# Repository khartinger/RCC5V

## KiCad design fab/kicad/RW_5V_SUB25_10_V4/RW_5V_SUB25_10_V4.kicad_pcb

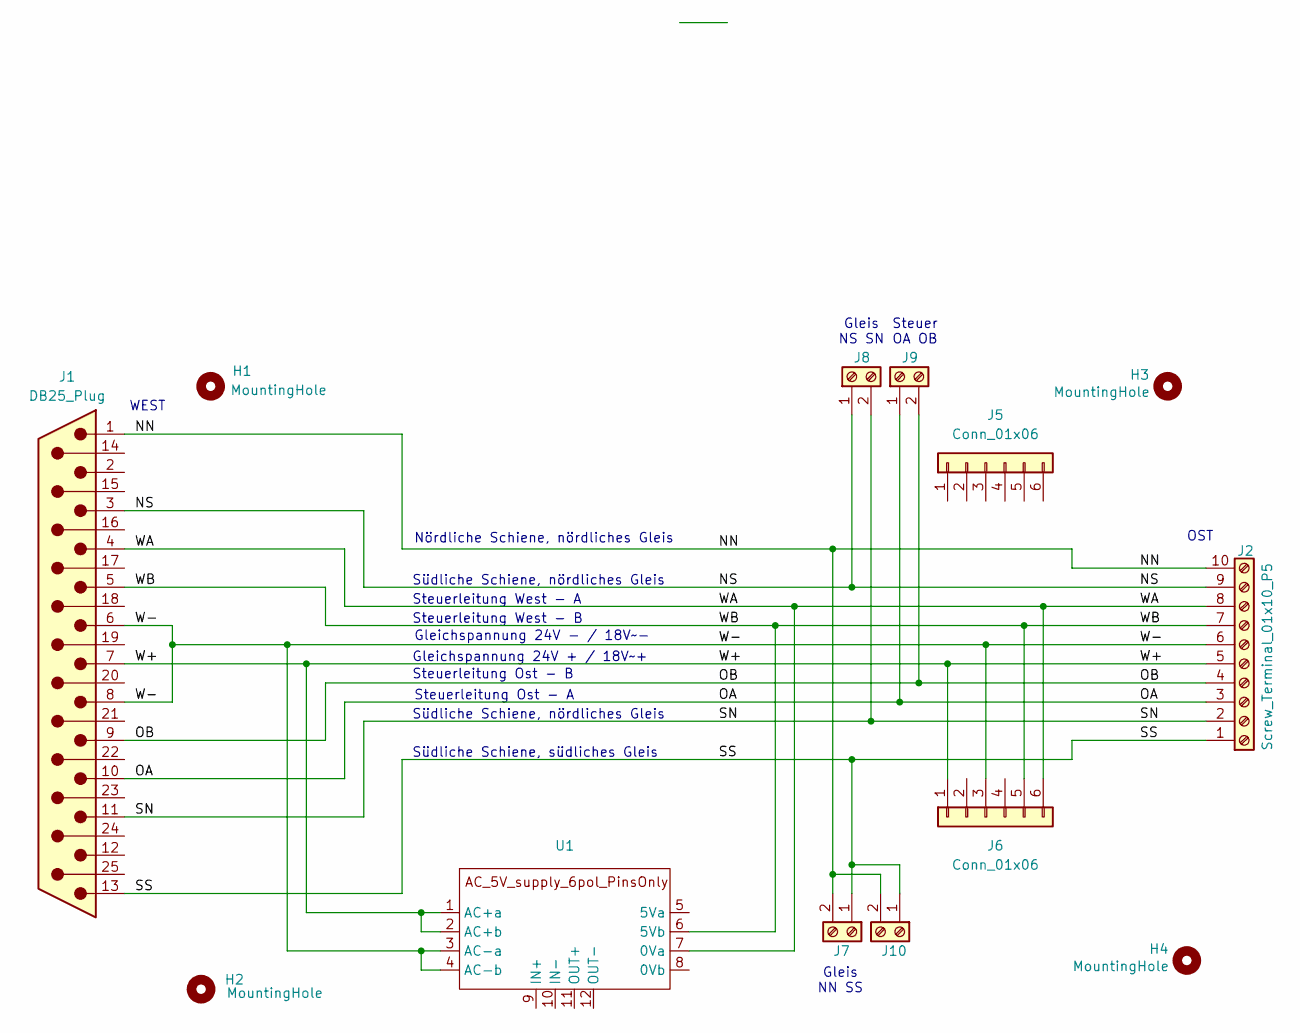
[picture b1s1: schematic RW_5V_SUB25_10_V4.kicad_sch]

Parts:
H1, H2, H3, H4: MountingHole; MountingHole_2.7mm_M2.5_DIN965_Pad_TopBottom
J1: DB25_Plug; DSUB-25_Male_Horizontal_P2.77x2.84mm_EdgePinOffset7.70mm_Ho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
J2: Screw_Terminal_01x10_P5
J5, J6: Conn_01x06; PinSocket_1x06_P2.54mm_Vertical_1.1_kh
J7, J8, J9, J10: Screw_Terminal_01x02_P5
U1: AC_5V_supply_6pol_PinsOnly

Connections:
/NN: J1.1, J2.10, J7.2, J10.2
/NS: J1.3, J2.9, J8.1
/OA: J1.10, J2.3, J9.1
/OB: J1.9, J2.4, J9.2
/SN: J1.11, J2.2, J8.2
/SS: J1.13, J2.1, J7.1, J10.1
/W+: J1.7, J2.5, J6.1, U1.1 (AC+a), U1.2 (AC+b)
/W-: J1.6, J1.8, J2.6, J6.3, U1.3 (AC-a), U1.4 (AC-b)
/WA: J1.4, J2.8, J6.6, U1.7 (0Va)
/WB: J1.5, J2.7, J6.5, U1.6 (5Vb)

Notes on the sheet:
Gleis NS SN
Südliche Schiene, südliches Gleis
Südliche Schiene, nördliches Gleis
Steuer OA OB
Gleichspannung 24V - / 18V~-
Nördliche Schiene, nördliches Gleis
Steuerleitung West - A
Steuerleitung Ost - B
Steuerleitung West - B
WEST
Gleichspannung 24V + / 18V~+
OST
Gleis NN SS
Steuerleitung Ost - A

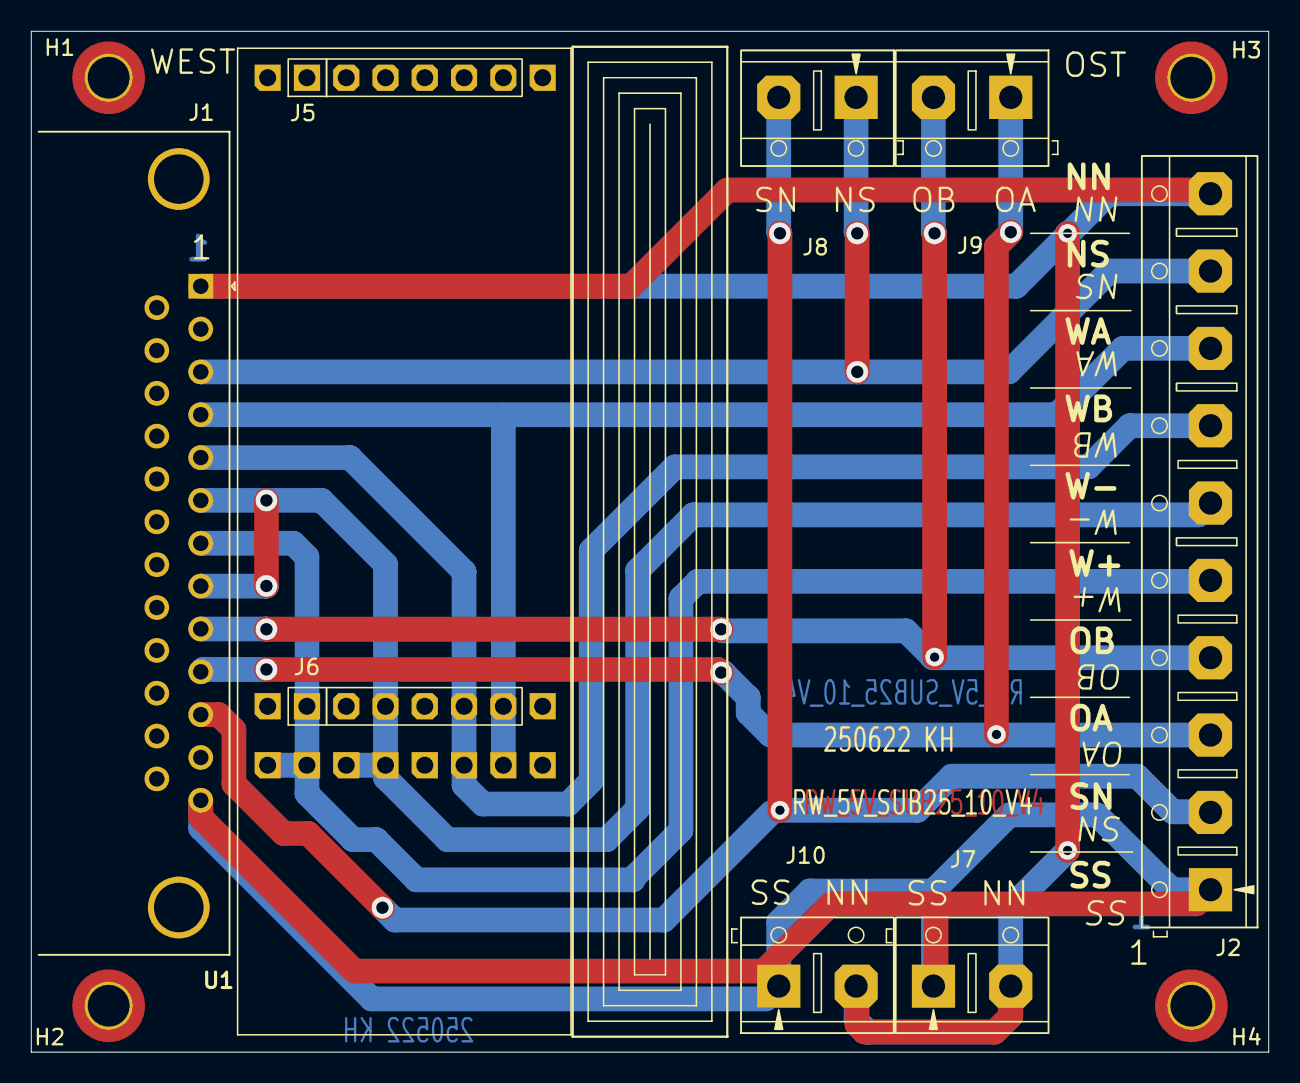
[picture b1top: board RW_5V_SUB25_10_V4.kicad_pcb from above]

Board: 2 copper layers, 80.0 x 66.0 mm, 13 parts (0 on the bottom side), 10 nets.

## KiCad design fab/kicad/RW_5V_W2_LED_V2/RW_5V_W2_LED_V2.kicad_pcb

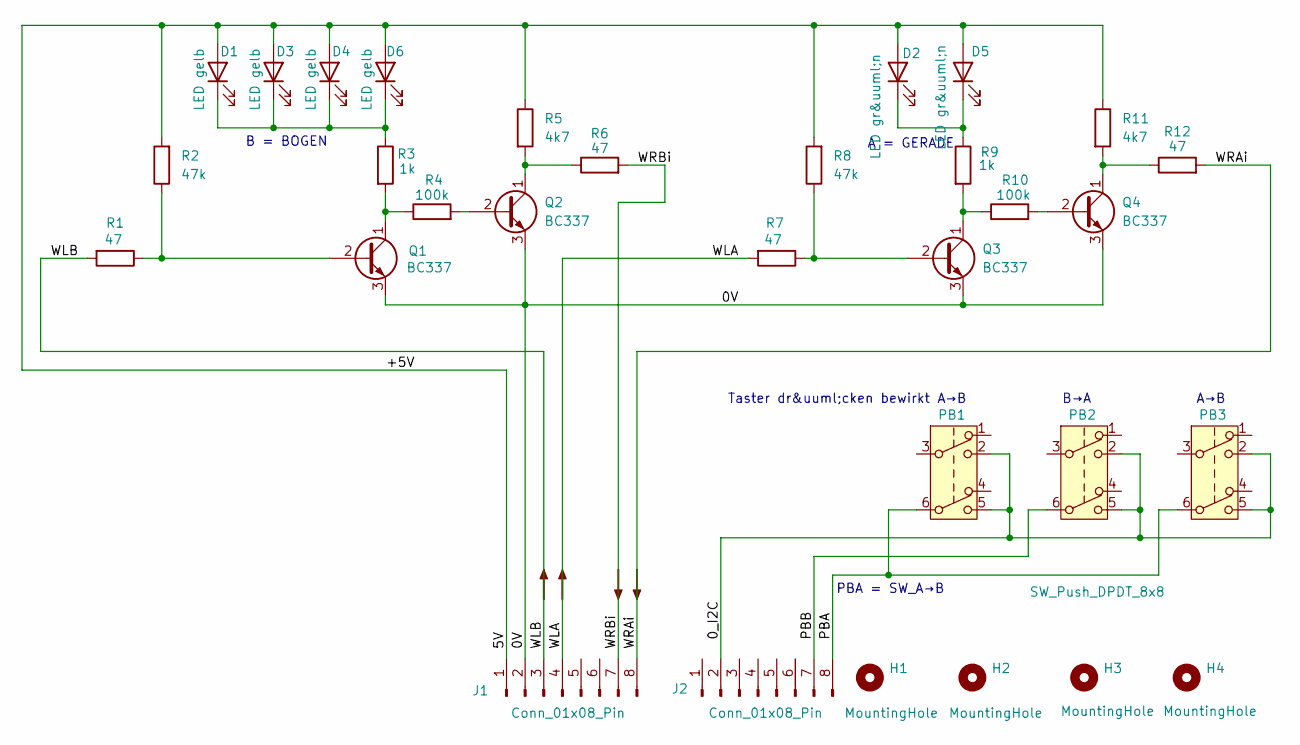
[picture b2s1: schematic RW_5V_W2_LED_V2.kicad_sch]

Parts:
D1, D3, D4, D6: LED gelb; LED_D3.0mm
D2, D5: LED gr&uuml;n; LED_D3.0mm
H1, H2, H3, H4: MountingHole; MountingHole_2.2mm_M2_Pad_TopBottom_kh
J1, J2: Conn_01x08_Pin; PinSocket_1x08_P2.54mm_Vertical_kh
PB1, PB2, PB3: SW_Push_DPDT_8x8
Q1, Q2, Q3, Q4: BC337; TO-92_Inline_Wide_custom
R1, R12: 47; R_Axial_DIN0204_L3.6mm_D1.6mm_P3.81mm_Vertical_kh
R2, R8: 47k; R_Axial_DIN0204_L3.6mm_D1.6mm_P2.54mm_Vertical
R3, R9: 1k; R_Axial_DIN0204_L3.6mm_D1.6mm_P2.54mm_Vertical
R4: 100k; R_Axial_DIN0204_L3.6mm_D1.6mm_P2.54mm_Vertical
R5, R11: 4k7; R_Axial_DIN0204_L3.6mm_D1.6mm_P2.54mm_Vertical
R6: 47; R_Axial_DIN0204_L3.6mm_D1.6mm_P2.54mm_Vertical
R7: 47; R_Axial_DIN0204_L3.6mm_D1.6mm_P2.54mm_Vertical_kh
R10: 100k; R_Axial_DIN0204_L3.6mm_D1.6mm_P2.54mm_Vertical_kh

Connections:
/0V: J1.2, Q1.3 (E), Q2.3 (E), Q3.3 (E), Q4.3 (E)
/0_I2C: J2.2, PB1.2 (B), PB1.5 (B), PB2.2 (B), PB2.5 (B), PB3.2 (B), PB3.5 (B)
/+5V: D1.2 (A), D2.2 (A), D3.2 (A), D4.2 (A), D5.2 (A), D6.2 (A), J1.1, R2.2, R5.1, R8.2, R11.1
/PBA: J2.8, PB1.6 (C), PB3.6 (C)
/PBB: J2.7, PB2.6 (C)
/WLA: J1.4, R7.2
/WLB: J1.3, R1.2
/WRAi: J1.8, R12.2
/WRBi: J1.7, R6.2
unnamed: D1.1 (K), D3.1 (K), D4.1 (K), D6.1 (K), R3.1
unnamed: D2.1 (K), D5.1 (K), R9.1
unnamed: Q1.2 (B), R1.1, R2.1
unnamed: Q1.1 (C), R3.2, R4.1
unnamed: Q2.2 (B), R4.2
unnamed: Q2.1 (C), R5.2, R6.1
unnamed: Q3.2 (B), R7.1, R8.1
unnamed: Q3.1 (C), R9.2, R10.1
unnamed: Q4.2 (B), R10.2
unnamed: Q4.1 (C), R11.2, R12.1

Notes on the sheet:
PBA = SW_A→B
A = GERADE
A→B
B→A
B = BOGEN
Taster dr&uuml;cken bewirkt

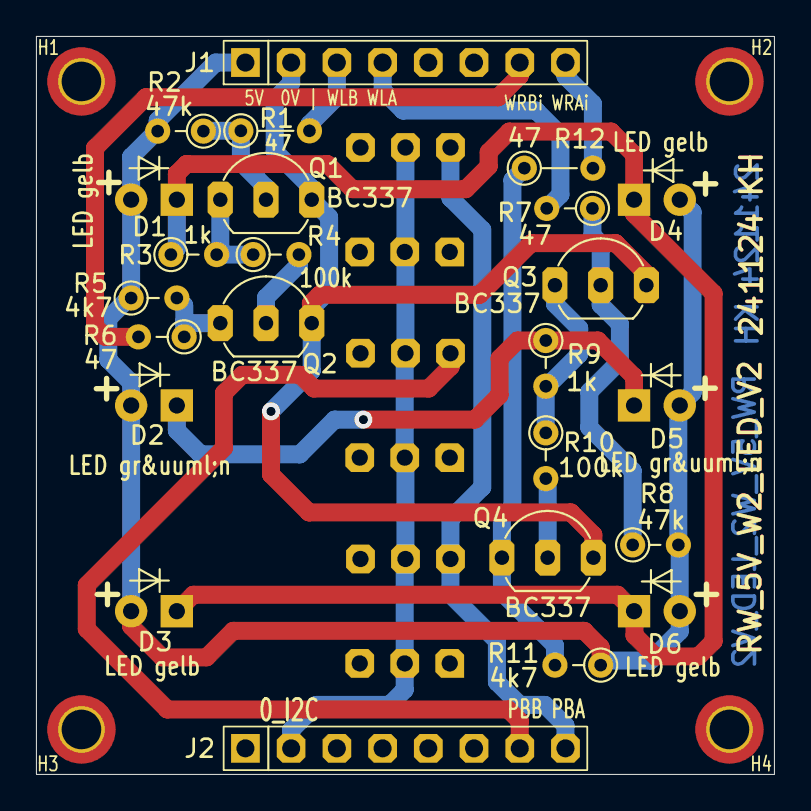
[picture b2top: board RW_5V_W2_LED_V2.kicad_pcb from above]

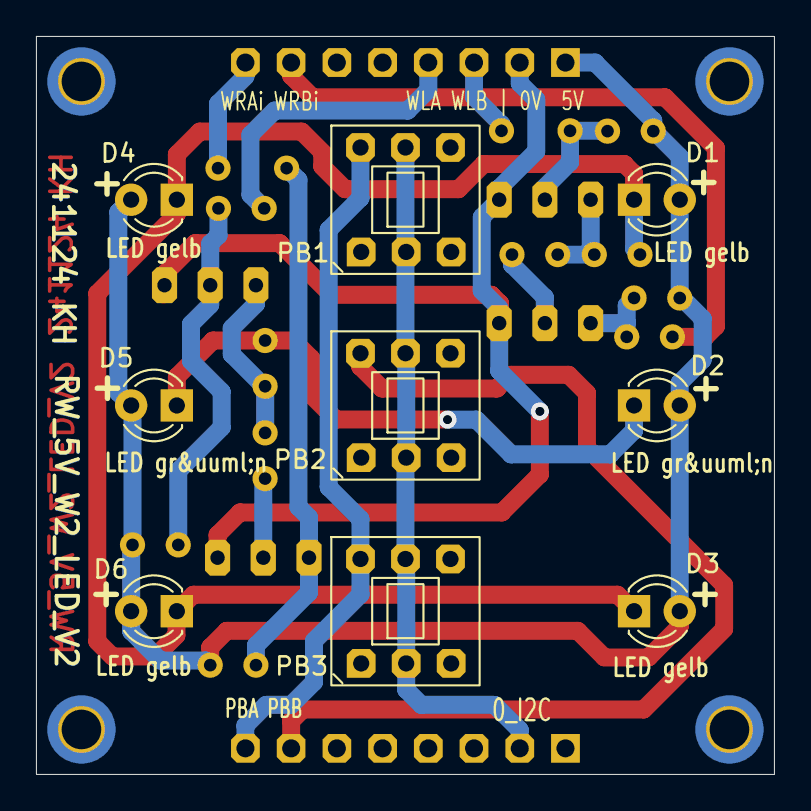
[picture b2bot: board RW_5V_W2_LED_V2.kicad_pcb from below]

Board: 2 copper layers, 41.0 x 41.0 mm, 31 parts (9 on the bottom side), 19 nets.

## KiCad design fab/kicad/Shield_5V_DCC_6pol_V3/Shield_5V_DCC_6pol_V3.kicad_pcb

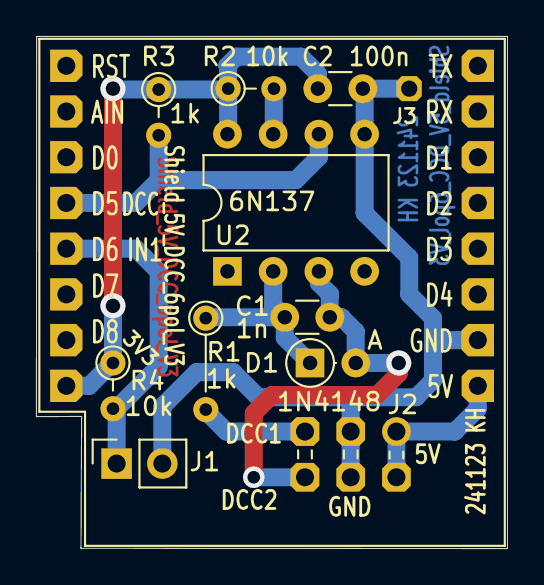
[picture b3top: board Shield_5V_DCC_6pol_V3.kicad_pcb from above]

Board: 2 copper layers, 26.2 x 28.4 mm, 12 parts (0 on the bottom side), 9 nets.

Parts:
C1: 1nF; C_Disc_D3.0mm_W1.6mm_P2.50mm
C2: 100nF; C_Disc_D3.0mm_W1.6mm_P2.50mm
D1: 1N4148; D_DO-35_SOD27_P2.54mm_Vertical_AnodeUp
J1: Conn_01x02_Socket; PinSocket_1x02_P2.54mm_Vertical
J2: Box_02x03_P2.54_Vertical; Box_02x03_P2.54mm_Horizontal_mini_kh
J3: Conn_01x01_kh; Pin_D0.9mm_W1.4mm
R1: 1k; R_Axial_DIN0204_L3.6mm_D1.6mm_P5.08mm_Vertical
R2, R4: 10k; R_Axial_DIN0204_L3.6mm_D1.6mm_P2.54mm_Vertical
R3: 1k; R_Axial_DIN0204_L3.6mm_D1.6mm_P2.54mm_Vertical
U1: WeMos_D1_mini; WEMOS_D1_mini_kh_shield_2
U2: 6N137; DIP-8_W7.62mm

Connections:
/3V3: C2.1, R2.1, R3.1, R4.1, U1.8 (3V3), U2.8 (VCC)
/5V: J2.1, J2.2, U1.9 (5V)
/DCC: R3.2, U1.4 (SCK/D5), U2.6 (VO)
/DCC1: J2.5, R1.2
/DCC2: C1.2, D1.2 (A), J2.6, U2.3 (C)
/GND: C2.2, J1.2, J2.3, J2.4, J3.1, U1.10 (GND), U2.5 (GND)
/IN1: J1.1, R4.2, U1.5 (MISO/D6)
unnamed: C1.1, D1.1 (K), R1.1, U2.2 (A)
unnamed: R2.2, U2.7 (EN)

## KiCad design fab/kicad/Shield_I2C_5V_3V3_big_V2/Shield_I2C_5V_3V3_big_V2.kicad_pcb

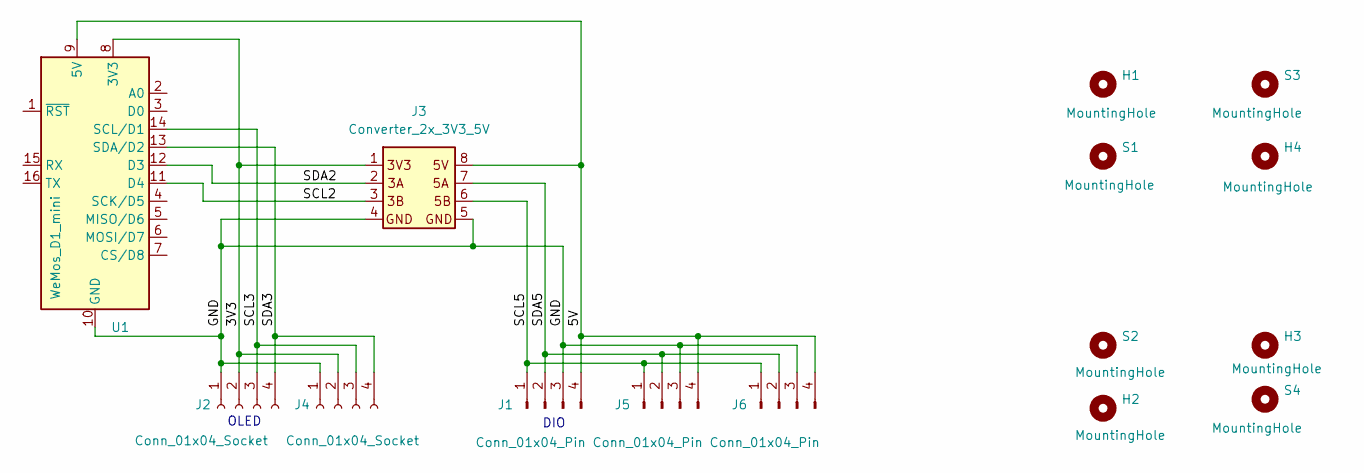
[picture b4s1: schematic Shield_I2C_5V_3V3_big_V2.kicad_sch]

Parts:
H1, H2, H3, H4: MountingHole; MountingHole_2.2mm_M2_Pad_TopBottom_kh
J1, J5, J6: Conn_01x04_Pin; PinSocket_1x04_P2.54mm_Vertical_kh
J2, J4: Conn_01x04_Socket; PinSocket_1x04_P2.54mm_Vertical_kh
J3: Converter_2x_3V3_5V
S1, S2, S3, S4: MountingHole; Hole_3.2mm_M3_Pad_TopBottom_kh
U1: WeMos_D1_mini; WEMOS_D1_mini_kh_shield_2

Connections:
/3V3: J2.2, J3.1, J4.2, U1.8 (3V3)
/5V: J1.4, J3.8, J5.4, J6.4, U1.9 (5V)
/GND: J1.3, J2.1, J3.4 (PIN_4), J3.5, J4.1, J5.3, J6.3, U1.10 (GND)
/SCL2: J3.3, U1.11 (D4)
/SCL3: J2.3, J4.3, U1.14 (SCL/D1)
/SCL5: J1.1, J3.6, J5.1, J6.1
/SDA2: J3.2 (3A), U1.12 (D3)
/SDA3: J2.4, J4.4, U1.13 (SDA/D2)
/SDA5: J1.2, J3.7, J5.2, J6.2

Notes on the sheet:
DIO
OLED

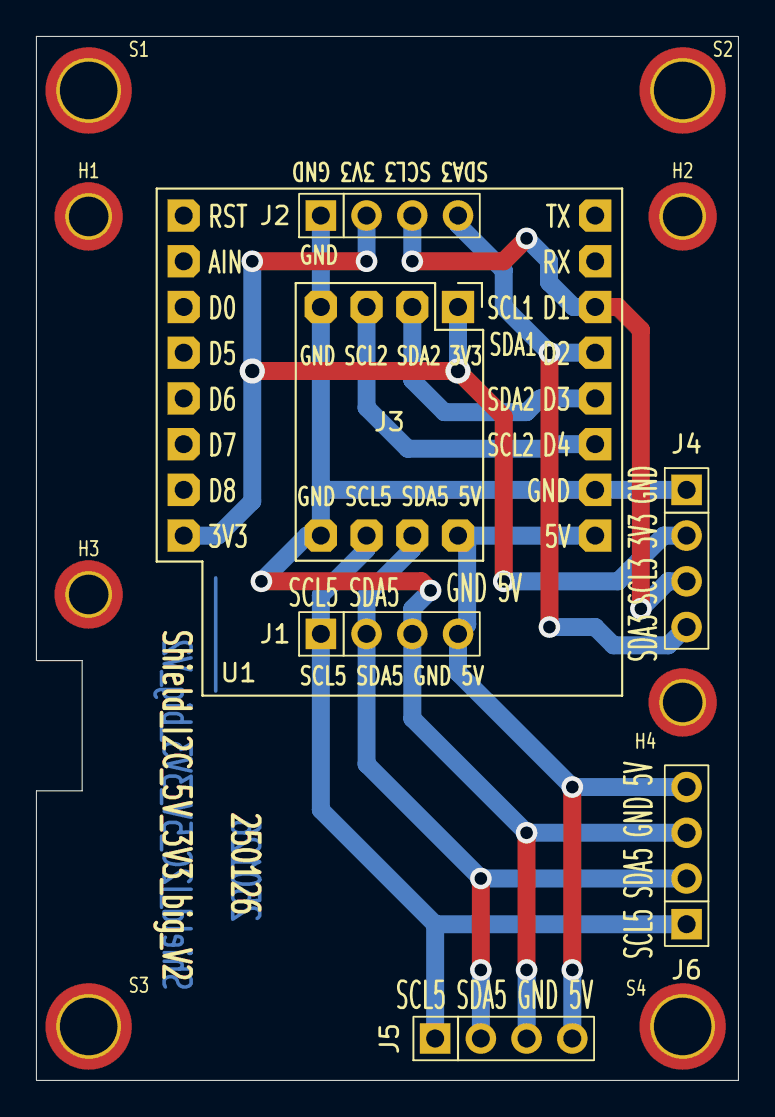
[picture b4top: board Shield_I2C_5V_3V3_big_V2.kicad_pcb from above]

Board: 2 copper layers, 39.0 x 58.0 mm, 15 parts (0 on the bottom side), 9 nets.
